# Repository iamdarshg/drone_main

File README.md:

### This thing has gotten too convoluted for me to continue, moved to drone-v2

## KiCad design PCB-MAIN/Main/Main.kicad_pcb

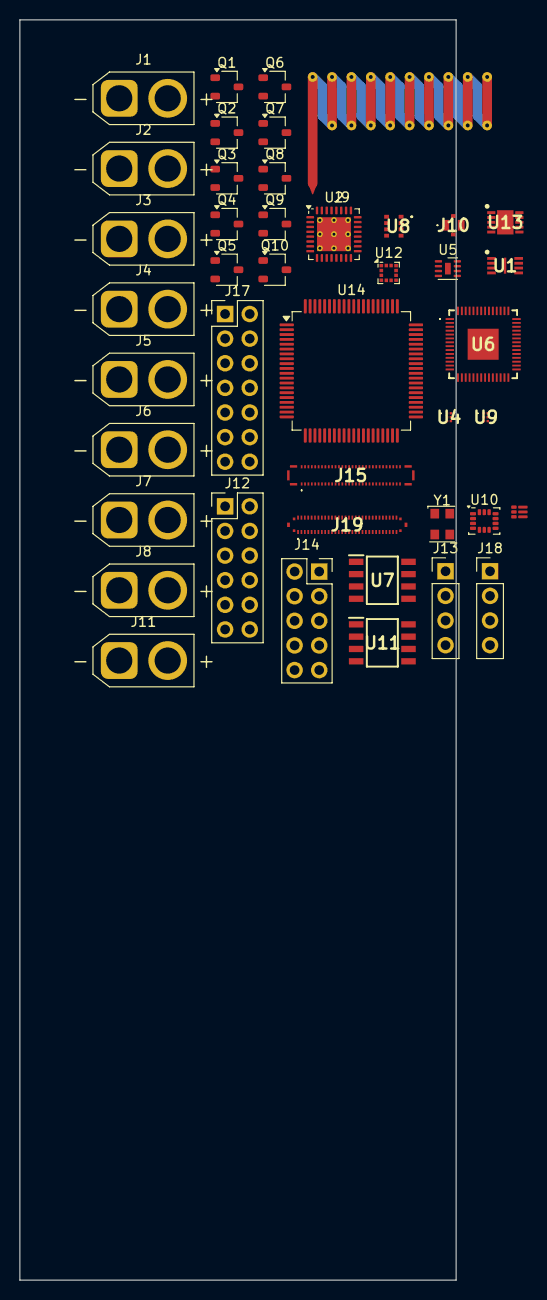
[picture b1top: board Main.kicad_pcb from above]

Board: 4 copper layers, 45.0 x 130.0 mm, 43 parts (0 on the bottom side), 87 nets, no tracks yet.

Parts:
J1, J2, J3, J4, J5, J6, J7, J8, J11: Conn_01x02; AMASS_XT30U-F_1x02_P5.0mm_Vertical
J9: Conn_01x01_Shielded; Texas_SWRA416_868MHz_915MHz
J10: Conn_01x04; MM80302610RK0
J12: SERVO-OUT-1; PinHeader_2x06_P2.54mm_Vertical
J13: SERVO-OUT-2; PinHeader_1x04_P2.54mm_Vertical
J14: BUS-DEBUG; PinSocket_2x05_P2.54mm_Vertical
J15: 216700-0609; 2167000609
J17: JTAG; PinHeader_2x07_P2.54mm_Vertical
J18: UART-OUT; PinHeader_1x04_P2.54mm_Vertical
J19: 216701-0609; 2167010609
Q1, Q2, Q3, Q4, Q5, Q6, Q7, Q8, Q9, Q10: Q_NMOS_GSD; SOT-23W
U1: IS25LP040E-JYLE-TR; SON50P300X200X60-9N
U2: STM32WL33KBV6; VQFN-32-1EP_5x5mm_P0.5mm_EP3.5x3.5mm_ThermalVias
U3: AP61402; V-DFN1515-6
U4, U9: LTE3401LX
U5: MIC2876; DFN-8-1EP_2x2mm_P0.5mm_EP0.6x1.2mm
U6: SC0914_13_; SC091413
U7, U11: NCV7344AD10R2G; SOIC127P600X175-8N
U8: ICP-10111; ICP10111
U10: LSM6DS3; LGA-14_3x2.5mm_P0.5mm_LayoutBorder3x4y
U12: KX122-1042; LGA-12_2x2mm_P0.5mm
U13: NX3DV221TKX; SON50P300X300X100-11N
U14: F28P550SG8PNAR; TQFP-80_12x12mm_P0.5mm
Y1: Crystal_GND24_Small; Oscillator_SMD_EuroQuartz_XO32-4Pin_3.2x2.5mm

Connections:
+1V2: U14.8 (VDD), U14.53 (VDD), U14.71 (VDD)
+3V3: J13.4, J19.33, J19.61 (MP1), J19.62 (MP2), J19.65 (MP5), U14.7 (VDDIO), U14.26 (VDDA), U14.52 (VDDIO), U14.72 (VDDIO)
+5V: J12.3, J12.4, J12.9, J12.10, J13.2
GND: J12.5, J12.6, J12.11, J12.12, J13.3, J19.34, J19.63 (MP3), J19.64 (MP4), J19.66 (MP6), U1.4 (GND), U1.9 (EP), U6.57 (GND), U14.9 (VSS), U14.25 (VSSA), U14.30 (VSS), U14.55 (VSS), U14.56 (VREGENZ), U14.70 (VSS), Y1.2, Y1.4
unnamed: J12.1, J15.59
unnamed: J12.2, J15.58
unnamed: J12.7, J15.60
unnamed: J12.8, J15.57
unnamed: J13.1, J15.56
unnamed: Q8.1 (G), U2.1 (PA2), U6.31 (GPIO20)
unnamed: J15.32, Q9.3 (D), U2.23 (PB7), U6.16 (GPIO13), U10.14 (SDA)
unnamed: Q9.2 (S), U8.3 (SDA)
unnamed: Q10.3 (D), U8.4 (SCL)
unnamed: Q9.1 (G), Q10.1 (G), U2.6 (PA10), U6.30 (GPIO19)
unnamed: J15.31, Q10.2 (S), U2.9 (PB6), U6.17 (GPIO14), U10.13 (SCL)
unnamed: U1.1 (CE#), U6.56 (QSPI_SS_N)
unnamed: U1.7 (HOLD#_(IO3)), U6.51 (QSPI_SD3)
unnamed: U1.6 (SCK), U6.52 (QSPI_SCLK)
unnamed: U1.5 (SI_(IO0)), U6.53 (QSPI_SD0)
unnamed: U1.2 (SO_(IO1)), U6.55 (QSPI_SD1)
unnamed: U1.3 (WP#_(IO2)), U6.54 (QSPI_SD2)
unnamed: U2.22 (PA1), U9.6 (CTRL)
unnamed: J15.20, U2.8 (PA8), U6.34 (GPIO22)
unnamed: J15.21, U2.7 (PA9), U6.32 (GPIO21)
unnamed: U2.30 (PB0), U4.6 (CTRL)
unnamed: J15.17, U2.31 (PB1), U6.36 (GPIO24)
unnamed: J15.19, U2.10 (PB12), U6.35 (GPIO23)
unnamed: J15.18, U2.11 (PB13), U6.37 (GPIO25)
unnamed: U2.12 (PB14), U6.27 (GPIO16)
unnamed: U2.13 (PB15), U6.28 (GPIO17)
unnamed: U2.15 (RX), U4.3 (RF_OUT)
unnamed: U2.17 (TX_HP), U9.5 (RF_IN)
unnamed: U6.6 (GPIO4), U7.4 (RXD)
unnamed: U6.7 (GPIO5), U7.1 (TXD)
unnamed: U6.8 (GPIO6), U7.8 (STB)
unnamed: U6.20 (XIN), Y1.1
unnamed: U6.21 (XOUT), Y1.3
unnamed: U2.5 (PA11), U6.29 (GPIO18), U10.12 (CS)
unnamed: J15.41, U12.12 (SCLK/SCL)
unnamed: J15.40, U12.2 (SDI/SDA)
unnamed: J15.39, U12.1 (SDO/ADDR)
unnamed: U2.2 (PA3), U12.4 (TRIG)
unnamed: U2.32 (PB2), U6.18 (GPIO15), U12.10 (~CS)
unnamed: J15.45, U13.3 (2D+)
unnamed: J15.44, U13.4 (2D-)
unnamed: J19.1, U14.19 (A0)
unnamed: J19.3, U14.18 (A1)
unnamed: J19.2, U14.15 (A14)
unnamed: J19.60, U14.63 (GPIO0)
unnamed: J19.18, U14.62 (GPIO1)
unnamed: J19.59, U14.61 (GPIO2)
unnamed: J19.17, U14.60 (GPIO3)
unnamed: J19.58, U14.59 (GPIO4)
unnamed: J19.57, U14.80 (GPIO6)
unnamed: J19.56, U14.58 (GPIO8)
unnamed: J19.55, U14.76 (GPIO10)
unnamed: J19.36, U14.37 (GPIO11)
unnamed: J19.35, U14.36 (GPIO12)
unnamed: J19.21, U14.79 (GPIO14)
unnamed: J19.20, U14.78 (GPIO15)
unnamed: J19.39, U14.39 (GPIO16)
unnamed: J19.40, U14.40 (GPIO17)
unnamed: J19.41, J19.47, U14.50 (GPIO18)
unnamed: J19.42, J19.46, U14.51 (GPIO19)
unnamed: J19.44, U14.65 (GPIO23)
unnamed: J19.28, U14.41 (GPIO24)
unnamed: J19.27, U14.42 (GPIO25)
unnamed: J19.26, U14.43 (GPIO26)
unnamed: J19.25, U14.44 (GPIO27)
unnamed: J19.5, U14.4 (GPIO28)
unnamed: J19.6, U14.3 (GPIO29)
unnamed: J19.12, U14.1 (GPIO30)
unnamed: J19.13, U14.2 (GPIO31)
unnamed: J19.32, U14.49 (GPIO32)
unnamed: J19.31, U14.38 (GPIO33)
unnamed: J19.19, U14.77 (GPIO34)
unnamed: J19.49, U14.48 (GPIO35)
unnamed: J19.51, U14.46 (GPIO37)
unnamed: J19.45, U14.66 (GPIO41)
unnamed: J19.14, U14.6 (GPIO46)
unnamed: J19.10, U14.13 (GPIO224)
unnamed: J19.16, U14.11 (GPIO226)
unnamed: J19.15, U14.10 (GPIO228)
unnamed: J19.9, U14.12 (GPIO242)
unnamed: J19.52, U14.45 (TCK)
unnamed: J19.50, U14.47 (TMS)
unnamed: J19.48, U14.5 (XRSn)

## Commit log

2025-04-05 added work doen so far on the IMU code and comms
2025-04-05 readme :D
2025-07-14 got a better structure in place, will review for errors and libs needed now
2025-07-14 some minor additions
2025-07-14 ai goes mad
2025-07-14 check
2025-07-14 ai did some stuff
2025-07-14 can cnfirm, things are looking up
2025-07-14 lotta stuff
2025-07-14 hey hes doing good isnt he
2025-09-10 more slop :D
2025-09-11 perplexity goat
2025-09-11 more perplexity
2025-09-11 mor slop
2025-09-11 a lot
2025-09-11 asas
2025-09-11 basics
2025-12-09 feat: Initial project setup with hardware and F' scaffolding
    This commit includes the initial setup of the project, including:
    - Moving the old code to a `deprecated` directory.
    - Adding the hardware files to a `hardware` directory.
    - Updating the schematic with the GPS module and other I/O connections.
    - Scaffolding the F' project with all the necessary components.
    - Implementing a PID controller for the control system.
2025-12-09 feat: Initial F' Project Skeleton and Architecture
    This commit establishes the initial skeleton for the new flight software based on NASA's F' framework. It includes the basic component structure for the HAL, sensors, core logic, and actuators.
    It also sets up the initial GDS configuration with telemetry and command dictionaries and creates a placeholder quadcopter example topology. An architectural correction was made to this example to us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
    This initial structure serves as a foundation for implementing the full flight software logic as requested.
2025-12-09 file system fixes, new direction, new hardware
2025-12-10 feat: Implement Core Logic and Integrate F' Framework
    This commit completes the initial implementation of the F' flight software. It includes the following major changes:
    - **Architectural Correction:** The quadcopter example has been updated with a proper control architecture, using a Mixer and Motor components.
    - **F' Framework Integration:** The build system has been set up, all components have been integrated into the F' framework, and the topology has been updated.
    - **Core Logic Implementation:** The HAL, sensor, and core logic components have been implemented with placeholder and basic logic to demonstrate data flow and functionality.
    - **Advanced Sensor Fusion:** An Extended Kalman
2025-12-11 gitignore
2025-12-11 proper deprecation, TODO : remove duplicates
2025-12-17 Update README to indicate project migration
